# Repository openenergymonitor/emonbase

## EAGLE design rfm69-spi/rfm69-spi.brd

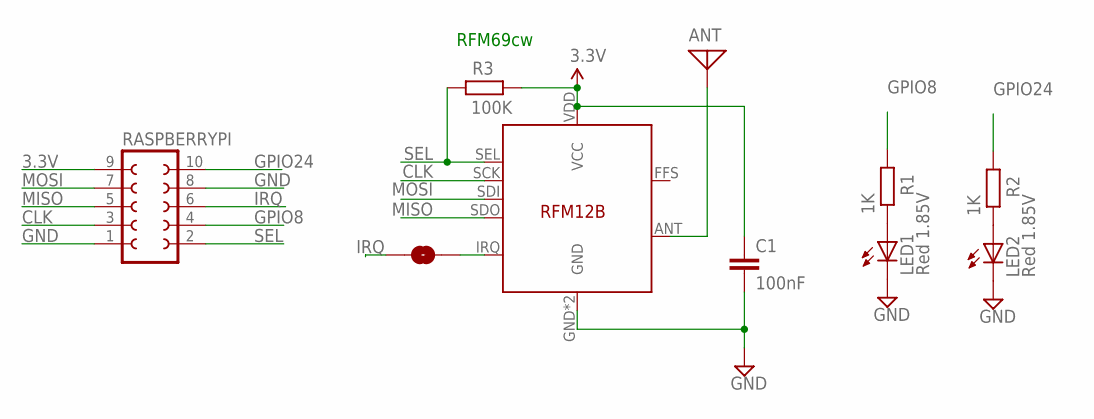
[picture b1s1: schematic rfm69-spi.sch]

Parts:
ANT: ANTENNA; PAD-01
C1: 100nF; C0603
GPIO15: SOLDERJUMPERNO; SJ_2S-NO
LED1, LED2: Red 1.85V; CHIP-LED0805
R1, R2: 1K; R0603
R3: 100K; R0603
RASPBERRYPI: FE05-2
U$14: RFM12B

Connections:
3.3V: C1.1, R3.1, RASPBERRYPI.9, U$14.VDD (VCC)
CLK: RASPBERRYPI.3, U$14.SCK
DIG1: ANT.1, U$14.ANT
GND: C1.2, LED1.C, LED2.C, RASPBERRYPI.1, RASPBERRYPI.8, U$14.GND, U$14.P$12 (GND)
GPIO8: R1.2, RASPBERRYPI.4
GPIO24: R2.2, RASPBERRYPI.10
IRQ: GPIO15.2, RASPBERRYPI.6
MISO: RASPBERRYPI.5, U$14.SDO
MOSI: RASPBERRYPI.7, U$14.SDI
unnamed: LED2.A, R2.1
unnamed: GPIO15.1, U$14.IRQ
unnamed: LED1.A, R1.1
SEL: R3.2, RASPBERRYPI.2, U$14.SEL

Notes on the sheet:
RFM69cw

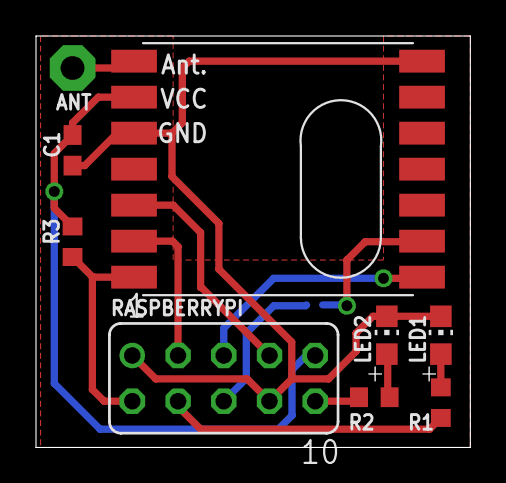
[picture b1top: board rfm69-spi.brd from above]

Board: 2 copper layers, 24.1 x 22.9 mm, 10 parts (1 on the bottom side), 13 nets.

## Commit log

2022-11-30 start on emonbase documentation
2022-11-30 rfm69-spi board files
2022-11-30 open hardware
2022-11-30 rfm69pi documentation
2022-12-01 Enable SPI docs
2023-01-25 update docs
2024-10-21 set default selPin 26 for emonBase RFM69 SPI
